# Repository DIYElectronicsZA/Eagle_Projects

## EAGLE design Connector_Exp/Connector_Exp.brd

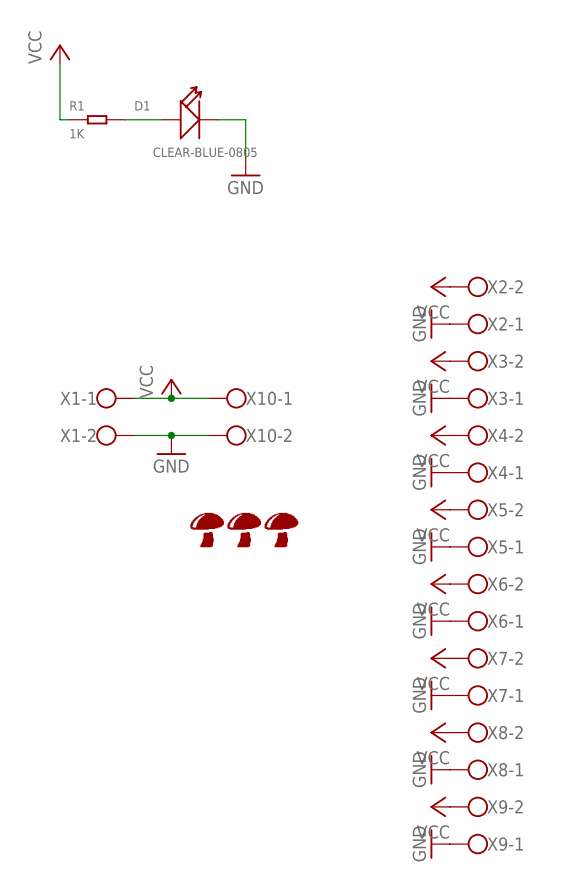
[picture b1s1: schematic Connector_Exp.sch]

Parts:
D1: CLEAR-BLUE-0805; LED-0805
R1: 1K; R0805
U$1: SHROOMTOPSILK; SHROOM_TS
U$2: SHROOMBOTTOMSILK; SHROOM_BS
U$3: SHROOM10MM
X1, X2, X3, X4, X5, X6, X7, X8, X9, X10: W237-102

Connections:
GND: D1.-, X1.2, X2.1, X3.1, X4.1, X5.1, X6.1, X7.1, X8.1, X9.1, X10.2
unnamed: D1.+, R1.2
VCC: R1.1, X1.1, X2.2, X3.2, X4.2, X5.2, X6.2, X7.2, X8.2, X9.2, X10.1

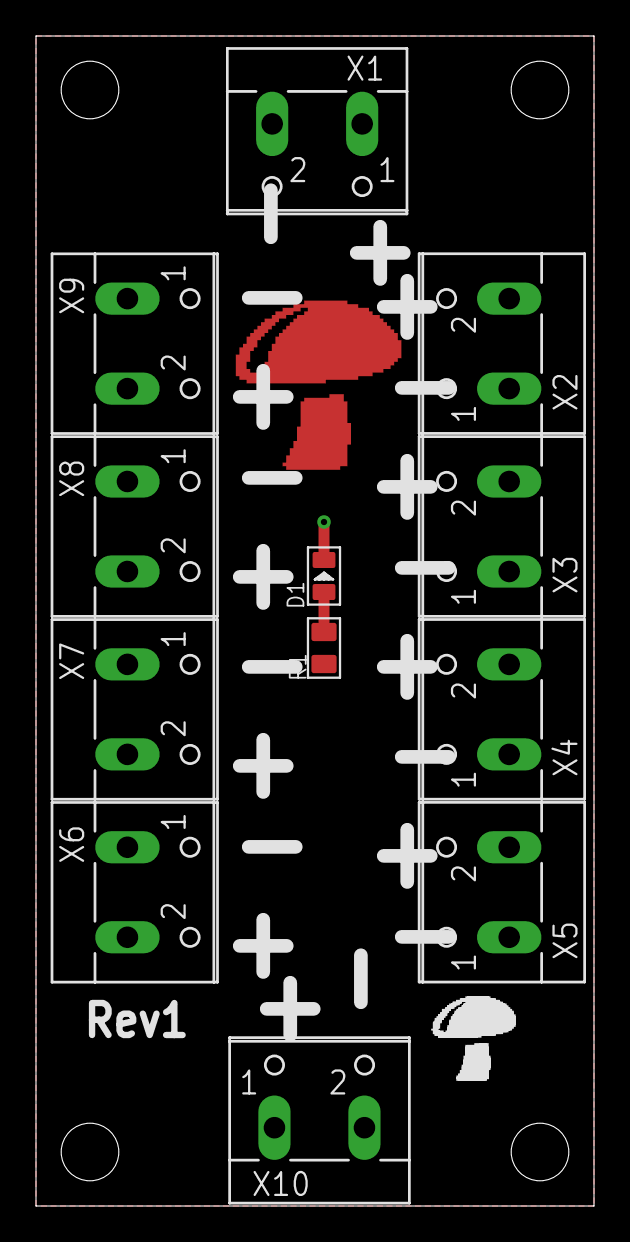
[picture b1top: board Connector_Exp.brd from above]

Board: 2 copper layers, 31.0 x 65.0 mm, 15 parts (0 on the bottom side), 3 nets.

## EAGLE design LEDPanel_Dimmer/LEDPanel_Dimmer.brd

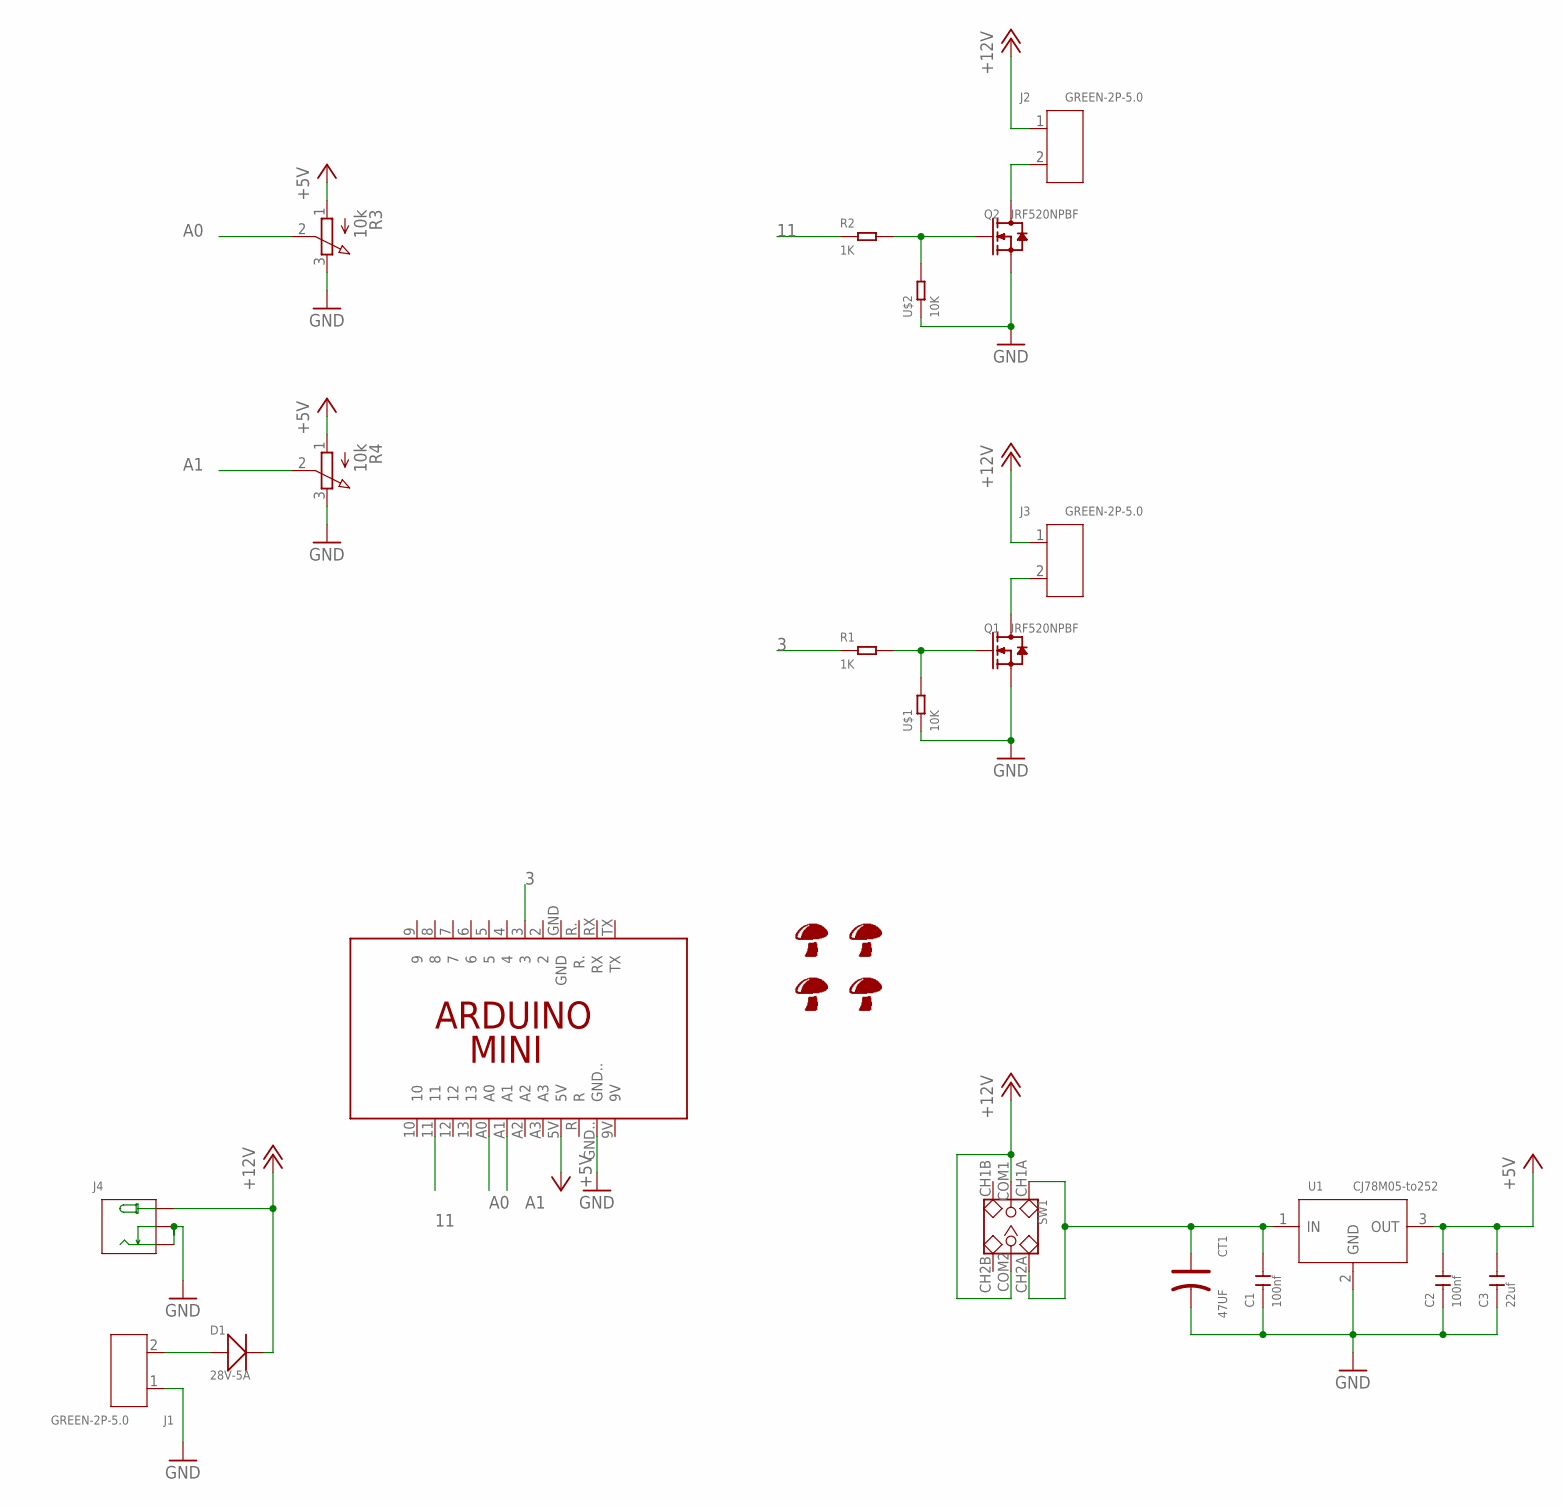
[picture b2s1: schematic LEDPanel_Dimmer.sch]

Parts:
C1, C2: 100nf; C0805
C3: 22uf; C0805
CT1: 47UF; ELECTRO-SMD-C-6MM
D1: 28V-5A; DO-214AA
J1, J2, J3: GREEN-2P-5.0; H2-5.0-10.5X8.0MM
J4: JACK-DC-005'DC-005'; 3P-L14.2*W11.0*H9.0MM
Q1, Q2: IRF520NPBF; TO-220
R1, R2: 1K; R0805
R3, R4: 10k; 3RP/1610N
SW1: DIP-TOGGLE-SWITCH-2CH-(2X3P-2.54); SW6-2.54-9.0X3.5X3.2+2.0MM
U1: CJ78M05-to252; TO-252
U$1, U$2: 10K; R0805
U$3: ARDUINO_MINI_REDUCED
U$4: SHROOMBOTTOMSILK; SHROOM_BS
U$5: SHROOMTOPSILK; SHROOM_TS
U$6: SHROOM10MM
U$7: SHROOM5MM; SHROOM

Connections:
3: R1.1, U$3.3
11: R2.1, U$3.11
+5V: C2.2, C3.2, R3.1 (A), R4.1 (A), U1.3 (OUT), U$3.5V
+12V: D1.-, J2.1, J3.1, J4.+, SW1.COM1, SW1.COM2
A0: R3.2 (S), U$3.A0
A1: R4.2 (S), U$3.A1
GND: C1.1, C2.1, C3.1, CT1.-, J1.1, J4.-1 (-), J4.-2 (CDN), Q1.3 (S), Q2.3 (S), R3.3 (E), R4.3 (E), U1.2 (GND), U$1.1, U$2.1, U$3.GND..
unnamed: D1.+, J1.2
unnamed: C1.2, CT1.+, SW1.CH1A, SW1.CH2A, U1.1 (IN)
unnamed: Q1.1 (G), R1.2, U$1.2
unnamed: J3.2, Q1.2 (D), Q1.HEAT (D)
unnamed: Q2.1 (G), R2.2, U$2.2
unnamed: J2.2, Q2.2 (D), Q2.HEAT (D)

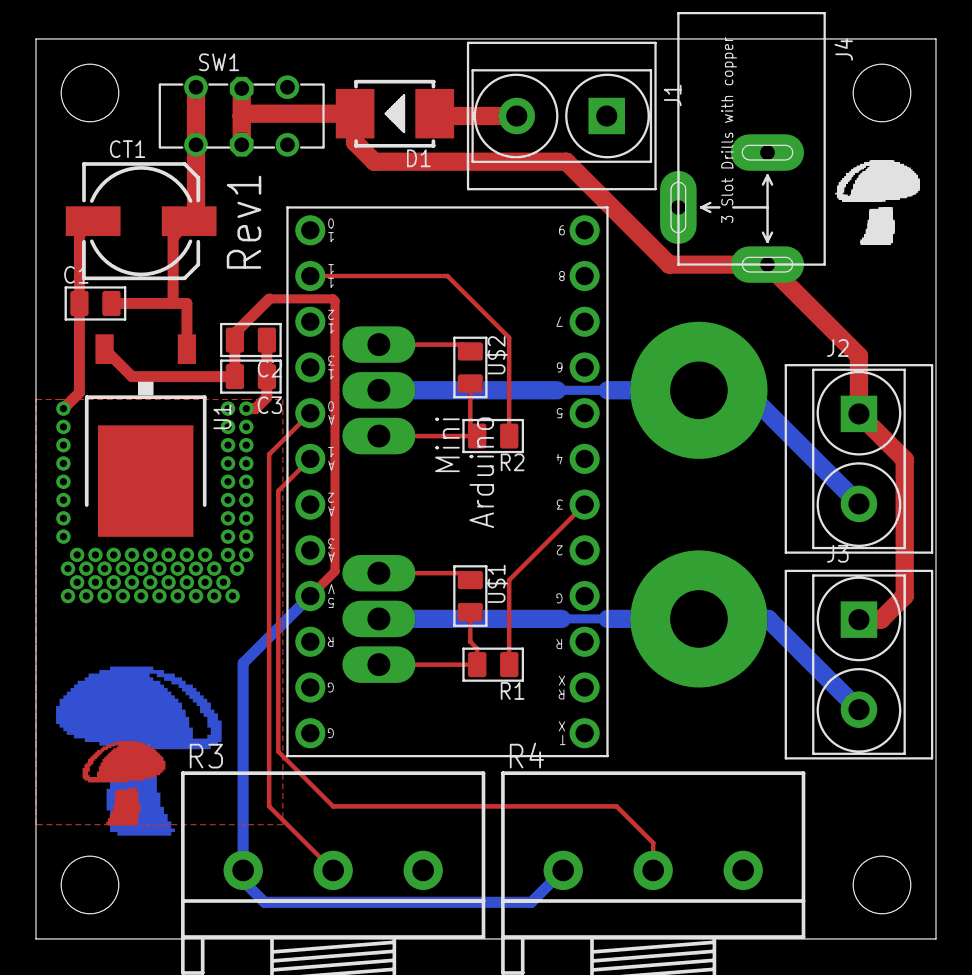
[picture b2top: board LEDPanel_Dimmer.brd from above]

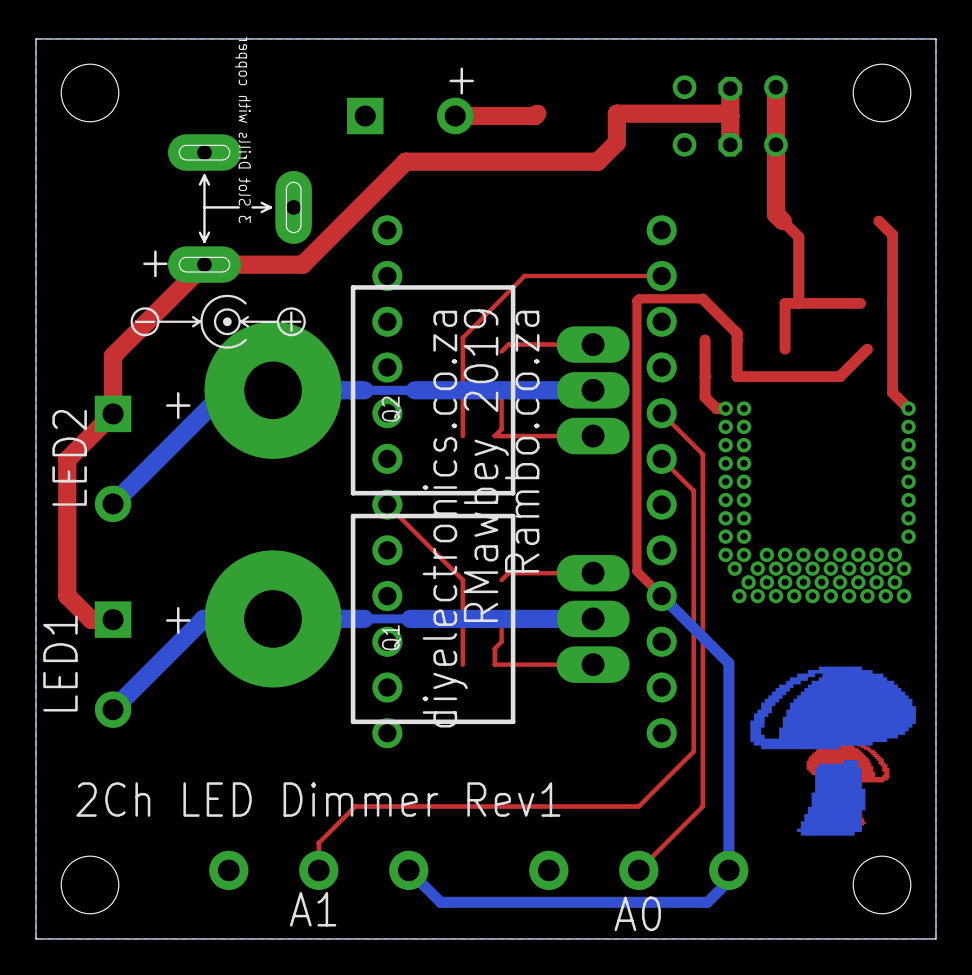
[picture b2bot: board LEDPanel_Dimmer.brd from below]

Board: 2 copper layers, 49.9 x 50.0 mm, 24 parts (3 on the bottom side), 13 nets.

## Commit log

2019-08-19 Octiboard first test
2019-08-21 Sent for production! V1 :D
2019-10-17 New Quick Eagle Projects
